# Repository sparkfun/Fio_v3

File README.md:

Fio v3
======

[  
*Fio v3-ATmega32U4 (DEV-11520)*](https://www.sparkfun.com/products/11520)

The Fio v3 is a ATmega32U4 powered system, similar to the ARduino Fio. This board is compatible with a Lipo battery and XBees, and 
runs at 3.3v and 8MHz. 

Repository Contents
-------------------
* **/Firmware** - Arduino example code used in the hookup guide
* **/Hardware** - All Eagle design files (.brd, .sch, .STL)
* **/Production** - Test bed files and production panel files

Documentation
--------------
* **[Hookup Guide](https://learn.sparkfun.com/tutorials/pro-micro--fio-v3-hookup-guide)** - Basic hookup guide for the FioV3.
* **[SparkFun Arduino Board Addon](https://github.com/sparkfun/Arduino_Boards/)** - Arduino board addon for FioV3.
 
License Information
-------------------
This product is _**open source**_! 

Please review the LICENSE.md file for license information. 

If you have any questions or concerns on licensing, please contact techsupport@sparkfun.com.

Distributed as-is; no warranty is given.

- Your friends at SparkFun.

_<COLLABORATION CREDIT>_

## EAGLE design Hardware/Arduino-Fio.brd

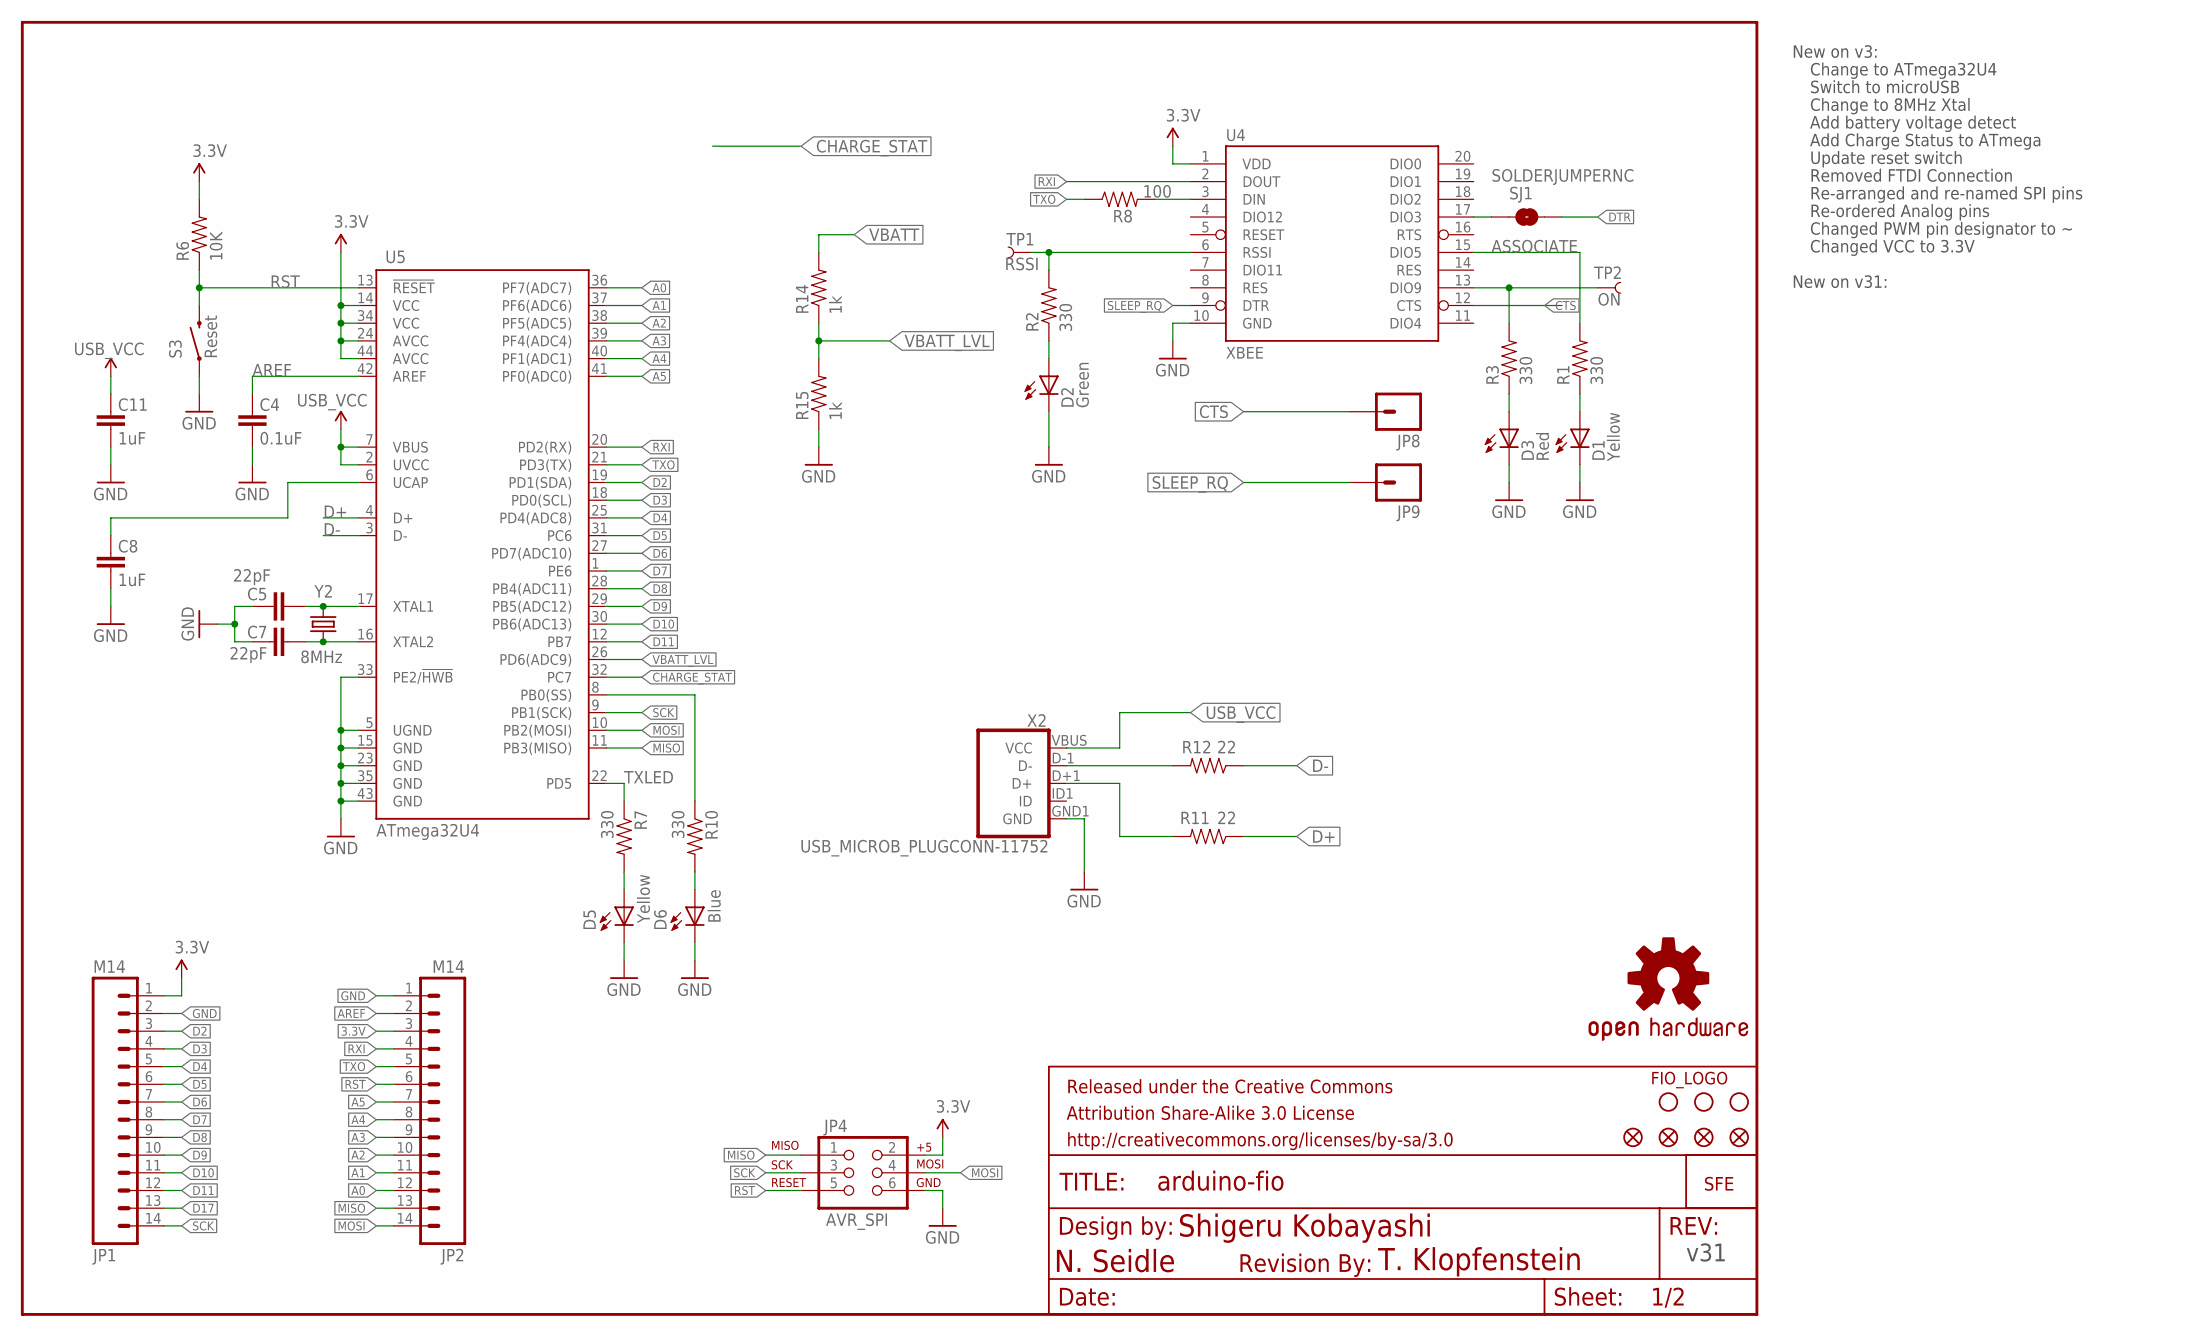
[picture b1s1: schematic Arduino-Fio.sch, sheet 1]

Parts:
C4: 0.1uF; 0603-CAP
C5, C7: 22pF; 0603-CAP
C8, C11: 1uF; 0603-CAP
D1, D5: Yellow; LED-0603
D2: Green; LED-0603
D3: Red; LED-0603
D6: Blue; LED-0603
FRAME1: FRAME-LETTER; CREATIVE_COMMONS
JP1, JP2: M14; 1X14
JP4: AVR_SPI; 2X3
JP5, JP16, JP17: STAND-OFF
JP8, JP9: M01PTH; 1X01
JP10, JP11, JP12, JP13: FIDUCIALUFIDUCIAL; FIDUCIAL-1X2
LOGO1: OSHW-LOGOL; OSHW-LOGO-L
R1, R2, R3, R7, R10: 330; 0603-RES
R6: 10K; 0603-RES
R8: 100; 0603-RES
R11, R12: 22; 0603-RES
R14, R15: 1k; 0603-RES
S3: Reset; TACTILE_SWITCH_SMD
SJ1: SOLDERJUMPERNC; SJ_2S
TP1: RSSI; PAD.03X.05
TP2: ON; PAD.03X.05
U4: XBEE; XBEE-SMD
U5: ATmega32U4; QFN-44-NOPAD_1:1
U$1: LOGO-SFENEW; SFE-NEW-WEBLOGO
U$2: REVISION
U$6: FIO_LOGOV2; FUNNEL_LOGO_BOTTOM_V2
X2: USB_MICROB_PLUGCONN-11752; USB-B-MICRO-SMD_V03
Y2: 8MHz; CRYSTAL-SMD-5X3

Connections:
3.3V: JP1.1, JP2.3, JP4.2, R6.2, U4.1 (VDD), U5.14 (VCC), U5.24 (AVCC), U5.34 (VCC), U5.44 (AVCC); also elsewhere on the board
A0: JP2.12, U5.36 (PF7(ADC7))
A1: JP2.11, U5.37 (PF6(ADC6))
A2: JP2.10, U5.38 (PF5(ADC5))
A3: JP2.9, U5.39 (PF4(ADC4))
A4: JP2.8, U5.40 (PF1(ADC1))
A5: JP2.7, U5.41 (PF0(ADC0))
AREF: C4.2, JP2.2, U5.42 (AREF)
ASSOCIATE: R1.2, U4.15 (DIO5)
CHARGE_STAT: U5.32 (PC7); also elsewhere on the board
CTS: JP8.1, U4.12 (CTS)
D2: JP1.3, U5.19 (PD1(SDA))
D3: JP1.4, U5.18 (PD0(SCL))
D4: JP1.5, U5.25 (PD4(ADC8))
D5: JP1.6, U5.31 (PC6)
D6: JP1.7, U5.27 (PD7(ADC10))
D7: JP1.8, U5.1 (PE6)
D8: JP1.9, U5.28 (PB4(ADC11))
D9: JP1.10, U5.29 (PB5(ADC12))
D10: JP1.11, U5.30 (PB6(ADC13))
D11: JP1.12, U5.12 (PB7)
D17: JP1.13, R10.1, U5.8 (PB0(SS))
D+: R11.1, U5.4 (D+)
D-: R12.1, U5.3 (D-)
DTR: SJ1.2
GND: C4.1, C5.2, C7.2, C8.1, C11.1, D1.C, D2.C, D3.C, D5.C, D6.C, JP1.2, JP2.1, JP4.6, R15.1, S3.1, U4.10 (GND), U5.5 (UGND), U5.15 (GND), U5.23 (GND), U5.33 (PE2/!HWB), U5.35 (GND), U5.43 (GND), X2.GND1 (GND); also elsewhere on the board
MISO: JP2.13, JP4.1, U5.11 (PB3(MISO))
MOSI: JP2.14, JP4.4, U5.10 (PB2(MOSI))
unnamed: R3.2, TP2.P$1, U4.13 (DIO9)
unnamed: D1.A, R1.1
unnamed: D2.A, R2.1
unnamed: R2.2, TP1.P$1, U4.6 (RSSI)
unnamed: R11.2, X2.D+1 (D+)
unnamed: D3.A, R3.1
unnamed: R8.2, U4.3 (DIN)
unnamed: SJ1.1, U4.17 (DIO3)
unnamed: D5.A, R7.2
unnamed: C7.1, U5.16 (XTAL2), Y2.1
unnamed: C5.1, U5.17 (XTAL1), Y2.3 (2)
unnamed: D6.A, R10.2
unnamed: R12.2, X2.D-1 (D-)
RST: JP2.6, JP4.5, R6.1, S3.3 (2), U5.13 (!RESET)
RXI: JP2.4, U4.2 (DOUT), U5.20 (PD2(RX))
SCK: JP1.14, JP4.3, U5.9 (PB1(SCK))
SLEEP_RQ: JP9.1, U4.9 (DTR)
TXLED: R7.1, U5.22 (PD5)
TXO: JP2.5, R8.1, U5.21 (PD3(TX))
UCAP: C8.2, U5.6 (UCAP)
USB_VCC: C11.2, U5.2 (UVCC), U5.7 (VBUS), X2.VBUS (VCC); also elsewhere on the board
VBATT: R14.2; also elsewhere on the board
VBATT_LVL: R14.1, R15.2, U5.26 (PD6(ADC9))

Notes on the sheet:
Shigeru Kobayashi
Change to ATmega32U4
Switch to microUSB
New on v3:
Change to 8MHz Xtal
Add battery voltage detect
Add Charge Status to ATmega
Update reset switch
Removed FTDI Connection
Re-arranged and re-named SPI pins
Re-ordered Analog pins
Changed PWM pin designator to ~
Changed VCC to 3.3V
New on v31:
v31
N. Seidle
T. Klopfenstein

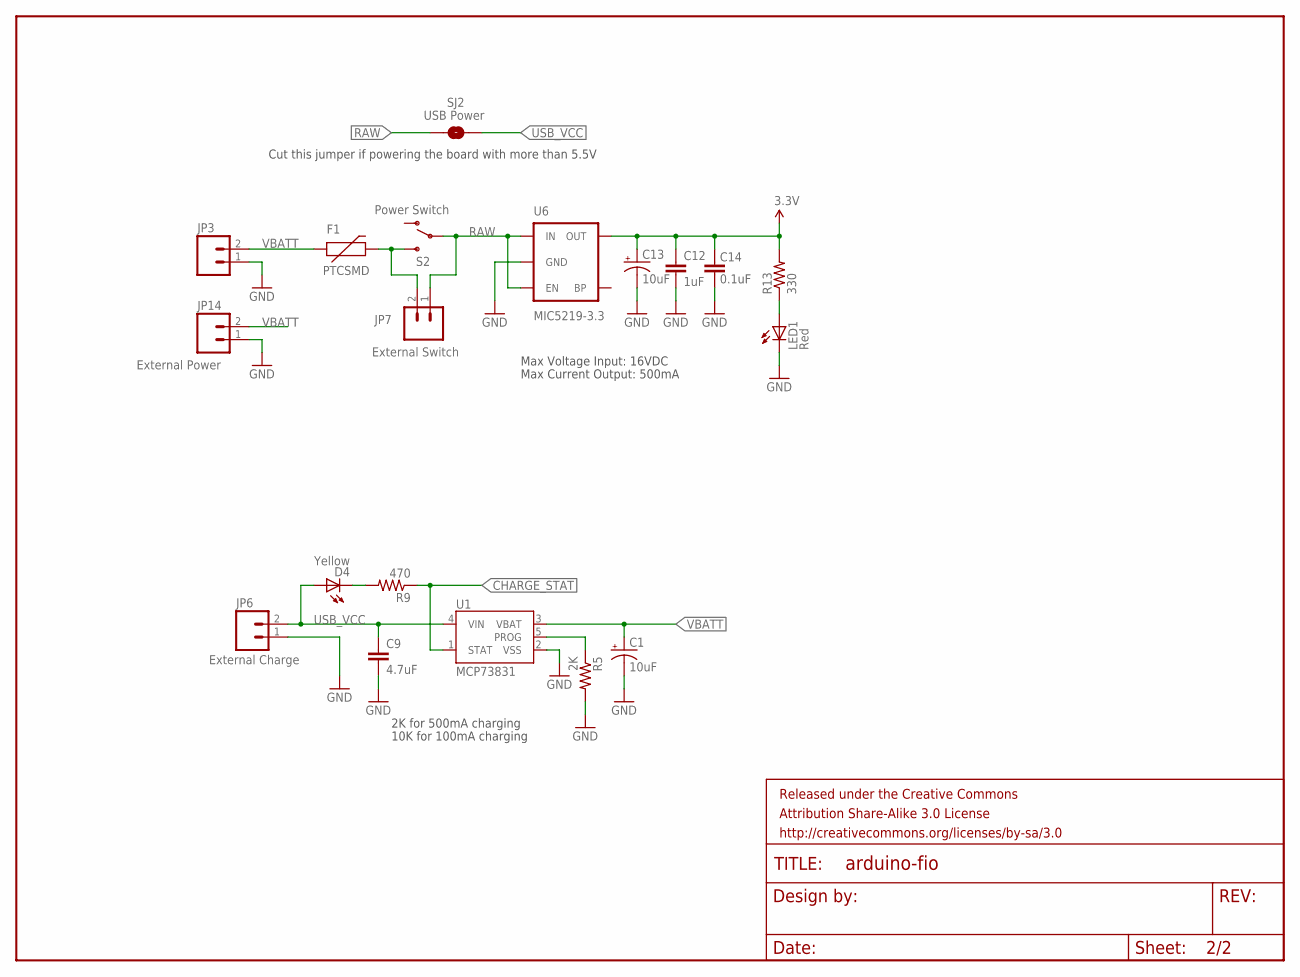
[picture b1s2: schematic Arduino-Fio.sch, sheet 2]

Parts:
C1, C13: 10uF; EIA3216
C9: 4.7uF; 0603-CAP
C12: 1uF; 0603-CAP
C14: 0.1uF; 0603-CAP
D4: Yellow; LED-0603
F1: PTCSMD; PTC-1206
FRAME2: FRAME-LETTER; CREATIVE_COMMONS
JP3: M02-JST-2MM-SMT; JST-2-SMD
JP6: External Charge; 1X02
JP7: External Switch; 1X02
JP14: External Power; 1X02
LED1: Red; LED-0603
R5: 2K; 0603-RES
R9: 470; 0603-RES
R13: 330; 0603-RES
S2: Power Switch; AYZ0202
SJ2: USB Power; SJ_2S-TRACE
U1: MCP73831; SOT23-5
U6: MIC5219-3.3; SOT23-5

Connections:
3.3V: C12.1, C13.A (+), C14.2, R13.2, U6.5 (OUT); also elsewhere on the board
CHARGE_STAT: R9.1, U1.1 (STAT); also elsewhere on the board
GND: C1.C (-), C9.2, C12.2, C13.C (-), C14.1, JP3.1, JP6.1, JP14.1, LED1.C, R5.2, U1.2 (VSS), U6.2 (GND); also elsewhere on the board
unnamed: D4.C, R9.2
unnamed: F1.2, JP7.2, S2.3 (S)
unnamed: R5.1, U1.5 (PROG)
unnamed: LED1.A, R13.1
RAW: JP7.1, S2.2, SJ2.1, U6.1 (IN), U6.3 (EN)
USB_VCC: C9.1, D4.A, JP6.2, SJ2.2, U1.4 (VIN); also elsewhere on the board
VBATT: C1.A (+), F1.1, JP3.2, JP14.2, U1.3 (VBAT); also elsewhere on the board

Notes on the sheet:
Max Voltage Input: 16VDC
Max Current Output: 500mA
Cut this jumper if powering the board with more than 5.5V
2K for 500mA charging
10K for 100mA charging

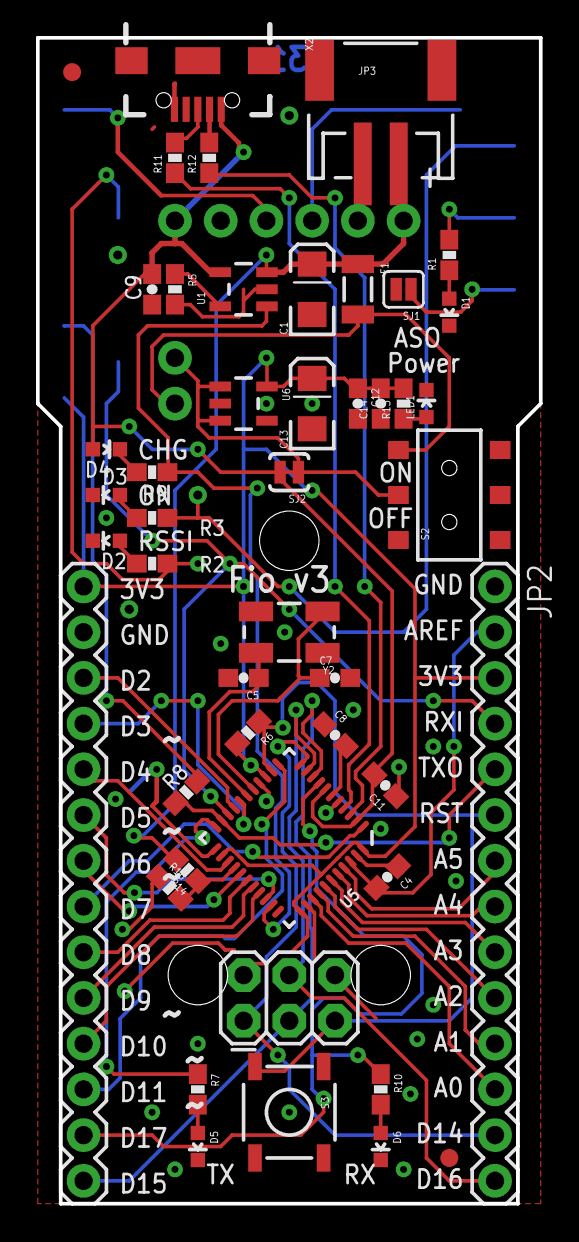
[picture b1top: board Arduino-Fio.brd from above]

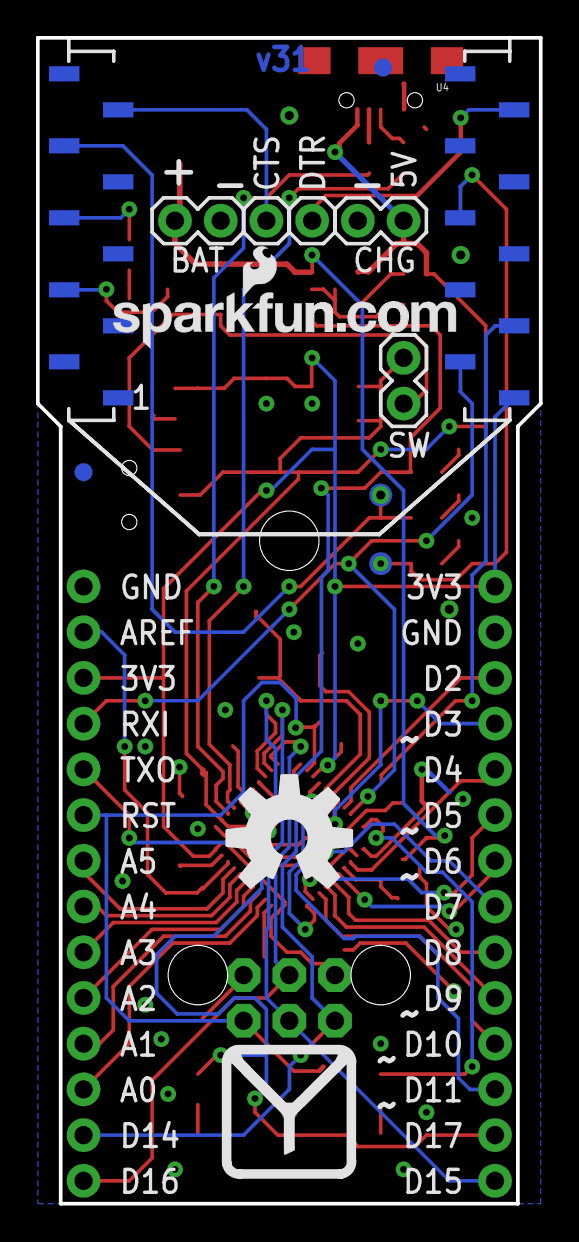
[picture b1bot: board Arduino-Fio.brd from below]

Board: 2 copper layers, 27.9 x 64.8 mm, 66 parts (12 on the bottom side), 55 nets.

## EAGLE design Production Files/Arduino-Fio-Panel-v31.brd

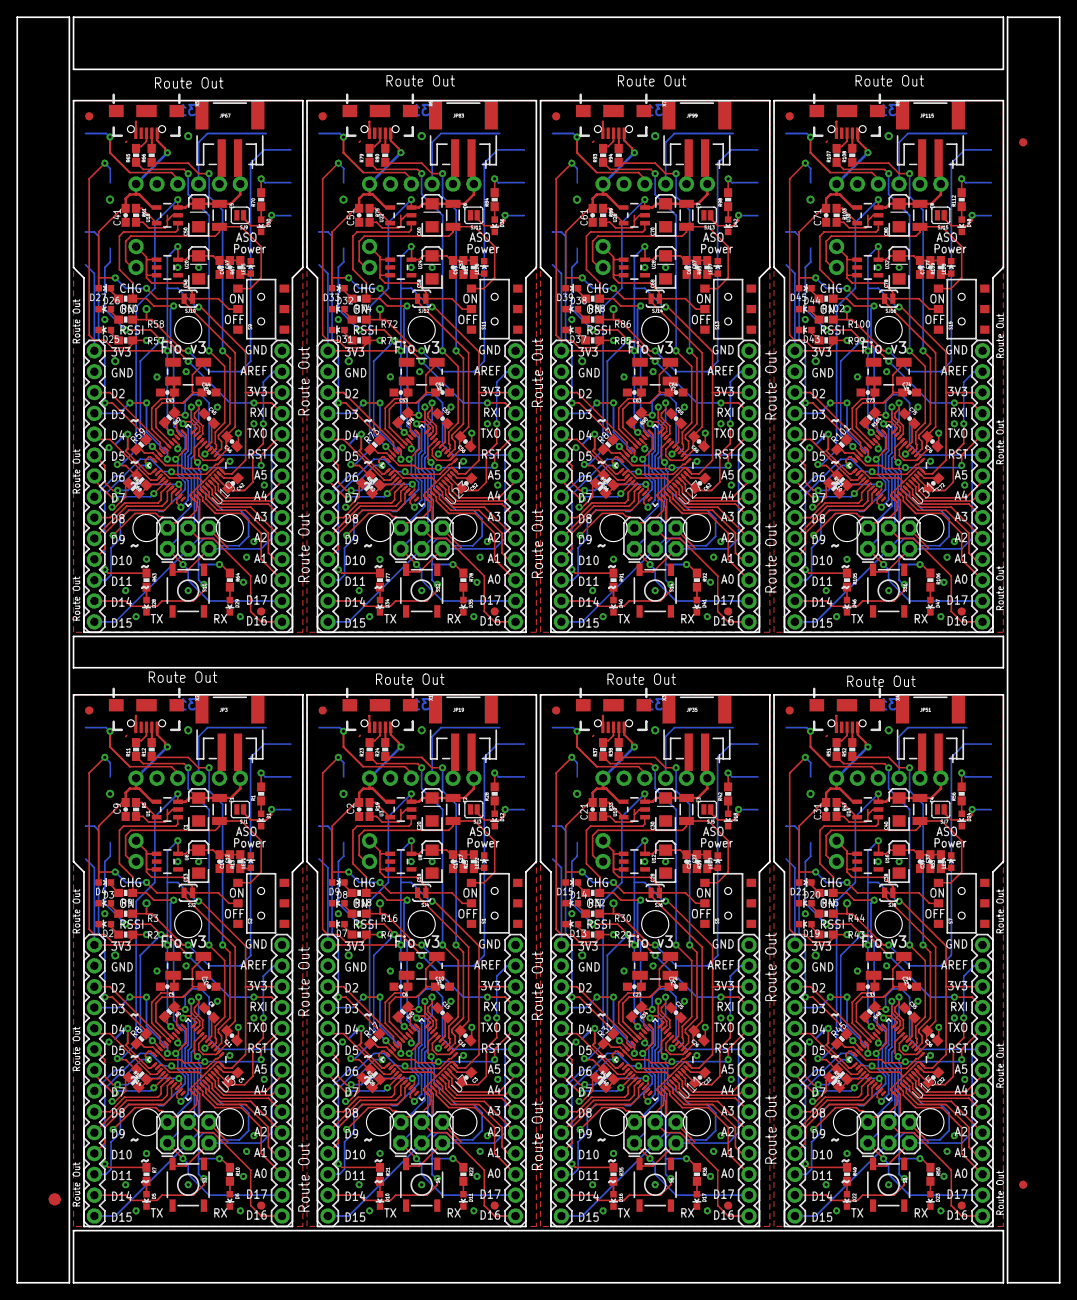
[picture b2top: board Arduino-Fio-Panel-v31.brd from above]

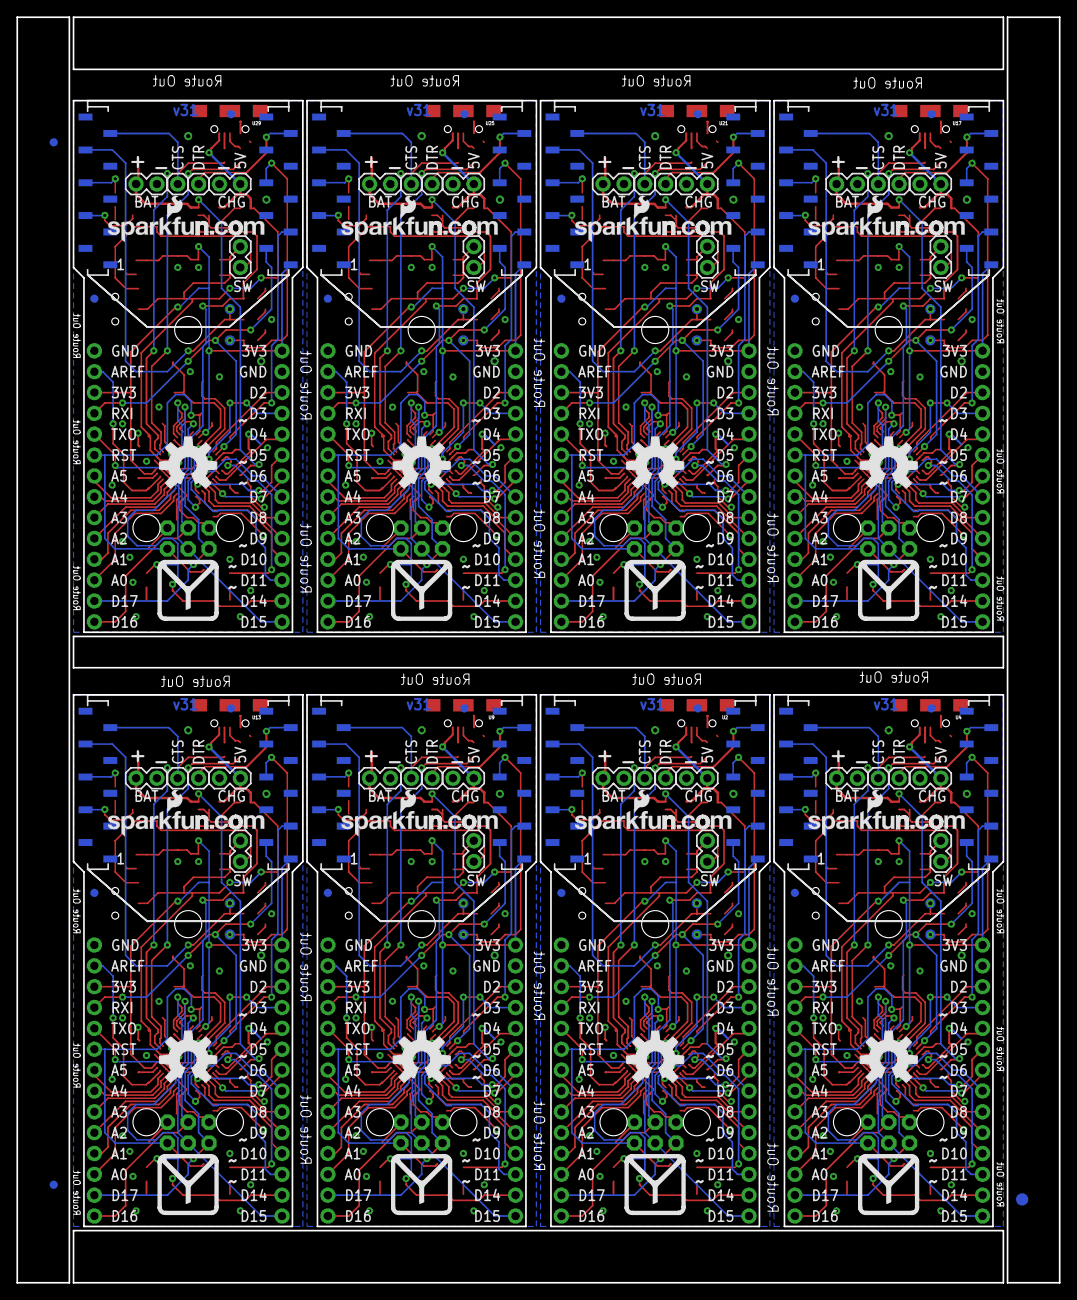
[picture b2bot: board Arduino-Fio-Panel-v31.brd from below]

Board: 2 copper layers, 127.0 x 154.2 mm, 510 parts (99 on the bottom side), 440 nets.

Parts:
C1, C13, C18, C20, C28, C30, C38, C40, C48, C50, C58, C60, C68, C70, C78, C80: 10uF; EIA3216
C2, C9, C21, C31, C41, C51, C61, C71: 4.7uF; 0603-CAP
C3, C4, C14, C19, C22, C29, C32, C39, C42, C49, C52, C59, C62, C69, C72, C79: 0.1uF; 0603-CAP
C5, C6, C7, C10, C23, C24, C33, C34, C43, C44, C53, C54, C63, C64, C73, C74: 22pF; 0603-CAP
C8, C11, C12, C15, C16, C17, C25, C26, C27, C35, C36, C37, C45, C46, C47, C55, C56, C57, C65, C66, C67, C75, C76, C77: 1uF; 0603-CAP
D1, D4, D5, D9, D10, D12, D15, D16, D18, D21, D22, D24, D27, D28, D30, D33, D34, D36, D39, D40, D42, D45, D46, D48: Yellow; LED-0603
D2, D7, D13, D19, D25, D31, D37, D43: Green; LED-0603
D3, D8, D14, D20, D26, D32, D38, D44: Red; LED-0603
D6, D11, D17, D23, D29, D35, D41, D47: Blue; LED-0603
E$1, E$2: FIDUCIAL-1.5X3
E$3, E$4, E$5, E$6: FIDUCIAL-1X2
F1, F2, F3, F4, F5, F6, F7, F8: PTCSMD; PTC-1206
JP1, JP2, JP18, JP29, JP34, JP45, JP50, JP61, JP66, JP77, JP82, JP93, JP98, JP109, JP114, JP125: M14; 1X14
JP3, JP19, JP35, JP51, JP67, JP83, JP99, JP115: JST-2-SMD
JP4, JP15, JP33, JP49, JP65, JP81, JP97, JP113: AVR_SPI; 2X3
JP5, JP16, JP17, JP30, JP31, JP32, JP46, JP47, JP48, JP62, JP63, JP64, JP78, JP79, JP80, JP94, JP95, JP96, JP110, JP111, JP112, JP126, JP127, JP128: STAND-OFF
JP6, JP21, JP37, JP53, JP69, JP85, JP101, JP117: External Charge; 1X02
JP7, JP22, JP38, JP54, JP70, JP86, JP102, JP118: External Switch; 1X02
JP8, JP9, JP23, JP24, JP39, JP40, JP55, JP56, JP71, JP72, JP87, JP88, JP103, JP104, JP119, JP120: 1X01
JP10, JP11, JP12, JP13, JP25, JP26, JP27, JP28, JP41, JP42, JP43, JP44, JP57, JP58, JP59, JP60, JP73, JP74, JP75, JP76, JP89, JP90, JP91, JP92, JP105, JP106, JP107, JP108, JP121, JP122, JP123, JP124: FIDUCIALUFIDUCIAL; FIDUCIAL-1X2
JP14, JP20, JP36, JP52, JP68, JP84, JP100, JP116: External Power; 1X02
LED1, LED2, LED3, LED4, LED5, LED6, LED7, LED8: Red; LED-0603
LOGO1, LOGO2, LOGO3, LOGO4, LOGO5, LOGO6, LOGO7, LOGO8: OSHW-LOGOL; OSHW-LOGO-L
R1, R2, R3, R4, R7, R10, R13, R16, R21, R22, R25, R28, R29, R30, R35, R36, R39, R42, R43, R44, R49, R50, R53, R56, R57, R58, R63, R64, R67, R70, R71, R72, R77, R78, R81, R84, R85, R86, R91, R92, R95, R98, R99, R100, R105, R106, R109, R112: 330; 0603-RES
R5, R19, R33, R47, R61, R75, R89, R103: 2K; 0603-RES
R6, R20, R34, R48, R62, R76, R90, R104: 10K; 0603-RES
R8, R17, R31, R45, R59, R73, R87, R101: 100; 0603-RES
R9, R18, R32, R46, R60, R74, R88, R102: 470; 0603-RES
R11, R12, R23, R24, R37, R38, R51, R52, R65, R66, R79, R80, R93, R94, R107, R108: 22; 0603-RES
R14, R15, R26, R27, R40, R41, R54, R55, R68, R69, R82, R83, R96, R97, R110, R111: 1k; 0603-RES
S1, S2, S5, S7, S9, S11, S13, S15: Power Switch; AYZ0202
S3, S4, S6, S8, S10, S12, S14, S16: Reset; TACTILE_SWITCH_SMD
SJ1, SJ3, SJ5, SJ7, SJ9, SJ11, SJ13, SJ15: SOLDERJUMPERNC; SJ_2S
SJ2, SJ4, SJ6, SJ8, SJ10, SJ12, SJ14, SJ16: USB Power; SJ_2S-TRACE
TP1, TP3, TP5, TP7, TP9, TP11, TP13, TP15: RSSI; PAD.03X.05
TP2, TP4, TP6, TP8, TP10, TP12, TP14, TP16: ON; PAD.03X.05
U1, U3, U10, U14, U18, U22, U26, U30: MCP73831; SOT23-5
U2, U4, U9, U13, U17, U21, U25, U29: XBEE; XBEE-SMD
U5, U7, U11, U15, U19, U23, U27, U31: ATMEGA32U4; QFN-44-NOPAD_1:1
U6, U8, U12, U16, U20, U24, U28, U32: MIC5219-3.3; SOT23-5
U$1, U$2, U$4, U$7, U$9, U$11, U$13, U$15: LOGO-SFENEW; SFE-NEW-WEBLOGO
U$3, U$5, U$6, U$8, U$10, U$12, U$14, U$16: FIO_LOGOV2; FUNNEL_LOGO_BOTTOM_V2
X1, X2, X3, X4, X5, X6, X7, X8: USB_MICROB_PLUGCONN-11752; USB-B-MICRO-SMD_V03
Y1, Y2, Y3, Y4, Y5, Y6, Y7, Y8: 8MHz; CRYSTAL-SMD-5X3

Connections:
3.3V: C12.1, C13.A, C14.2, JP1.1, JP2.3, JP4.2, R6.2, R13.2, U4.1, U5.14, U5.24, U5.34, U5.44, U6.5
3.3V1: C17.1, C18.A, C19.2, JP15.2, JP18.1, JP29.3, R20.2, R25.2, U2.1, U7.14, U7.24, U7.34, U7.44, U8.5
3.3V2: C27.1, C28.A, C29.2, JP33.2, JP34.1, JP45.3, R34.2, R39.2, U9.1, U11.14, U11.24, U11.34, U11.44, U12.5
3.3V3: C37.1, C38.A, C39.2, JP49.2, JP50.1, JP61.3, R48.2, R53.2, U13.1, U15.14, U15.24, U15.34, U15.44, U16.5
3.3V4: C47.1, C48.A, C49.2, JP65.2, JP66.1, JP77.3, R62.2, R67.2, U17.1, U19.14, U19.24, U19.34, U19.44, U20.5
3.3V5: C57.1, C58.A, C59.2, JP81.2, JP82.1, JP93.3, R76.2, R81.2, U21.1, U23.14, U23.24, U23.34, U23.44, U24.5
3.3V6: C67.1, C68.A, C69.2, JP97.2, JP98.1, JP109.3, R90.2, R95.2, U25.1, U27.14, U27.24, U27.34, U27.44, U28.5
3.3V7: C77.1, C78.A, C79.2, JP113.2, JP114.1, JP125.3, R104.2, R109.2, U29.1, U31.14, U31.24, U31.34, U31.44, U32.5
A0: JP2.12, U5.36
A1: JP2.11, U5.37
A2: JP2.10, U5.38
A3: JP2.9, U5.39
A4: JP2.8, U5.40
A5: JP2.7, U5.41
A6: JP29.12, U7.36
A7: JP29.11, U7.37
A8: JP29.10, U7.38
A9: JP29.9, U7.39
A10: JP29.8, U7.40
A11: JP29.7, U7.41
A12: JP45.12, U11.36
A13: JP45.11, U11.37
A14: JP45.10, U11.38
A15: JP45.9, U11.39
A16: JP45.8, U11.40
A17: JP45.7, U11.41
A18: JP61.12, U15.36
A19: JP61.11, U15.37
A20: JP61.10, U15.38
A21: JP61.9, U15.39
A22: JP61.8, U15.40
A23: JP61.7, U15.41
A24: JP77.12, U19.36
A25: JP77.11, U19.37
A26: JP77.10, U19.38
A27: JP77.9, U19.39
A28: JP77.8, U19.40
A29: JP77.7, U19.41
A30: JP93.12, U23.36
A31: JP93.11, U23.37
A32: JP93.10, U23.38
A33: JP93.9, U23.39
A34: JP93.8, U23.40
A35: JP93.7, U23.41
A36: JP109.12, U27.36
A37: JP109.11, U27.37
A38: JP109.10, U27.38
A39: JP109.9, U27.39
A40: JP109.8, U27.40
A41: JP109.7, U27.41
A42: JP125.12, U31.36
A43: JP125.11, U31.37
A44: JP125.10, U31.38
A45: JP125.9, U31.39
A46: JP125.8, U31.40
A47: JP125.7, U31.41
AREF: C4.2, JP2.2, U5.42
AREF1: C3.2, JP29.2, U7.42
AREF2: C22.2, JP45.2, U11.42
AREF3: C32.2, JP61.2, U15.42
AREF4: C42.2, JP77.2, U19.42
AREF5: C52.2, JP93.2, U23.42
AREF6: C62.2, JP109.2, U27.42
AREF7: C72.2, JP125.2, U31.42
ASSOCIATE: R1.2, U4.15
ASSOCIATE1: R28.2, U2.15
ASSOCIATE2: R42.2, U9.15
ASSOCIATE3: R56.2, U13.15
ASSOCIATE4: R70.2, U17.15
ASSOCIATE5: R84.2, U21.15
ASSOCIATE6: R98.2, U25.15
ASSOCIATE7: R112.2, U29.15
CHARGE_STAT: R9.1, U1.1, U5.32
CHARGE_STAT1: R18.1, U3.1, U7.32
CHARGE_STAT2: R32.1, U10.1, U11.32
CHARGE_STAT3: R46.1, U14.1, U15.32
CHARGE_STAT4: R60.1, U18.1, U19.32
CHARGE_STAT5: R74.1, U22.1, U23.32
CHARGE_STAT6: R88.1, U26.1, U27.32
CHARGE_STAT7: R102.1, U30.1, U31.32
CTS: JP8.1, U4.12
CTS1: JP23.1, U2.12
CTS2: JP39.1, U9.12
CTS3: JP55.1, U13.12
CTS4: JP71.1, U17.12
CTS5: JP87.1, U21.12
CTS6: JP103.1, U25.12
CTS7: JP119.1, U29.12
D1: JP18.3, U7.19
D2: JP1.3, U5.19
D3: JP1.4, U5.18
D4: JP1.5, U5.25
D5: JP1.6, U5.31
D6: JP1.7, U5.27
D7: JP1.8, U5.1
D8: JP1.9, U5.28
D9: JP1.10, U5.29
D10: JP1.11, U5.30
D11: JP1.12, U5.12
D12: JP18.4, U7.18
D13: JP18.5, U7.25
D14: JP1.13, R10.1, U5.8
D15: JP18.6, U7.31
D16: JP18.7, U7.27
D17: JP18.9, U7.28
D18: JP18.11, U7.30
D19: JP18.8, U7.1
D20: JP18.10, U7.29
D21: JP18.12, U7.12
D22: JP18.13, R22.1, U7.8
D23: JP34.3, U11.19
D24: JP34.4, U11.18
D25: JP34.5, U11.25
D26: JP34.6, U11.31
D27: JP34.7, U11.27
D28: JP34.9, U11.28
D29: JP34.11, U11.30
D30: JP34.8, U11.1
D31: JP34.10, U11.29
D32: JP34.12, U11.12
D33: JP34.13, R36.1, U11.8
D34: JP50.3, U15.19
D35: JP50.4, U15.18
D36: JP50.5, U15.25
D37: JP50.6, U15.31
D38: JP50.7, U15.27
D39: JP50.9, U15.28
D40: JP50.11, U15.30
D41: JP50.8, U15.1
D42: JP50.10, U15.29
D43: JP50.12, U15.12
D44: JP50.13, R50.1, U15.8
D45: JP66.3, U19.19
D46: JP66.4, U19.18
D47: JP66.5, U19.25
D48: JP66.6, U19.31
D49: JP66.7, U19.27
D50: JP66.9, U19.28
D51: JP66.11, U19.30
D52: JP66.8, U19.1
D53: JP66.10, U19.29
D54: JP66.12, U19.12
D55: JP66.13, R64.1, U19.8
D56: JP82.3, U23.19
D57: JP82.4, U23.18
D58: JP82.5, U23.25
D59: JP82.6, U23.31
D60: JP82.7, U23.27
D61: JP82.9, U23.28
D62: JP82.11, U23.30
D63: JP82.8, U23.1
D64: JP82.10, U23.29
D65: JP82.12, U23.12
D66: JP82.13, R78.1, U23.8
D67: JP98.3, U27.19
D68: JP98.4, U27.18
D69: JP98.5, U27.25
D70: JP98.6, U27.31
D71: JP98.7, U27.27
D72: JP98.9, U27.28
D73: JP98.11, U27.30
D74: JP98.8, U27.1
D75: JP98.10, U27.29
D76: JP98.12, U27.12
D77: JP98.13, R92.1, U27.8
D78: JP114.3, U31.19
D79: JP114.4, U31.18
D80: JP114.5, U31.25
D81: JP114.6, U31.31
D82: JP114.7, U31.27
D83: JP114.9, U31.28
D84: JP114.11, U31.30
D85: JP114.8, U31.1
D86: JP114.10, U31.29
D87: JP114.12, U31.12
D88: JP114.13, R106.1, U31.8
D+: R11.1, U5.4
D+1: R23.1, U7.4
D+2: R37.1, U11.4
D+3: R51.1, U15.4
D+4: R65.1, U19.4
D+5: R79.1, U23.4
D+6: R93.1, U27.4
D+7: R107.1, U31.4
D-: R12.1, U5.3
D-1: R24.1, U7.3
D-2: R38.1, U11.3
D-3: R52.1, U15.3
D-4: R66.1, U19.3
D-5: R80.1, U23.3
D-6: R94.1, U27.3
D-7: R108.1, U31.3
GND: C1.C, C4.1, C5.2, C7.2, C8.1, C9.2, C11.1, C12.2, C13.C, C14.1, D1.C, D2.C, D3.C, D5.C, D6.C, JP1.2, JP2.1, JP3.1, JP4.6, JP6.1, JP14.1, LED1.C, R5.2, R15.1, S3.1, U1.2, U4.10, U5.5, U5.15, U5.23, U5.33, U5.35, U5.43, U6.2, X2.GND1
GND1: C2.2, C3.1, C6.2, C10.2, C15.1, C16.1, C17.2, C18.C, C19.1, C20.C, D7.C, D8.C, D10.C, D11.C, D12.C, JP15.6, JP18.2, JP19.1, JP20.1, JP21.1, JP29.1, LED2.C, R19.2, R27.1, S4.1, U2.10, U3.2, U7.5, U7.15, U7.23, U7.33, U7.35, U7.43, U8.2, X1.GND1
GND2: C21.2, C22.1, C23.2, C24.2, C25.1, C26.1, C27.2, C28.C, C29.1, C30.C, D13.C, D14.C, D16.C, D17.C, D18.C, JP33.6, JP34.2, JP35.1, JP36.1, JP37.1, JP45.1, LED3.C, R33.2, R41.1, S6.1, U9.10, U10.2, U11.5, U11.15, U11.23, U11.33, U11.35, U11.43, U12.2, X3.GND1
GND3: C31.2, C32.1, C33.2, C34.2, C35.1, C36.1, C37.2, C38.C, C39.1, C40.C, D19.C, D20.C, D22.C, D23.C, D24.C, JP49.6, JP50.2, JP51.1, JP52.1, JP53.1, JP61.1, LED4.C, R47.2, R55.1, S8.1, U13.10, U14.2, U15.5, U15.15, U15.23, U15.33, U15.35, U15.43, U16.2, X4.GND1
GND4: C41.2, C42.1, C43.2, C44.2, C45.1, C46.1, C47.2, C48.C, C49.1, C50.C, D25.C, D26.C, D28.C, D29.C, D30.C, JP65.6, JP66.2, JP67.1, JP68.1, JP69.1, JP77.1, LED5.C, R61.2, R69.1, S10.1, U17.10, U18.2, U19.5, U19.15, U19.23, U19.33, U19.35, U19.43, U20.2, X5.GND1
GND5: C51.2, C52.1, C53.2, C54.2, C55.1, C56.1, C57.2, C58.C, C59.1, C60.C, D31.C, D32.C, D34.C, D35.C, D36.C, JP81.6, JP82.2, JP83.1, JP84.1, JP85.1, JP93.1, LED6.C, R75.2, R83.1, S12.1, U21.10, U22.2, U23.5, U23.15, U23.23, U23.33, U23.35, U23.43, U24.2, X6.GND1
GND6: C61.2, C62.1, C63.2, C64.2, C65.1, C66.1, C67.2, C68.C, C69.1, C70.C, D37.C, D38.C, D40.C, D41.C, D42.C, JP97.6, JP98.2, JP99.1, JP100.1, JP101.1, JP109.1, LED7.C, R89.2, R97.1, S14.1, U25.10, U26.2, U27.5, U27.15, U27.23, U27.33, U27.35, U27.43, U28.2, X7.GND1
GND7: C71.2, C72.1, C73.2, C74.2, C75.1, C76.1, C77.2, C78.C, C79.1, C80.C, D43.C, D44.C, D46.C, D47.C, D48.C, JP113.6, JP114.2, JP115.1, JP116.1, JP117.1, JP125.1, LED8.C, R103.2, R111.1, S16.1, U29.10, U30.2, U31.5, U31.15, U31.23, U31.33, U31.35, U31.43, U32.2, X8.GND1
MISO: JP2.13, JP4.1, U5.11
MISO1: JP15.1, JP29.13, U7.11
MISO2: JP33.1, JP45.13, U11.11
MISO3: JP49.1, JP61.13, U15.11
MISO4: JP65.1, JP77.13, U19.11
MISO5: JP81.1, JP93.13, U23.11
MISO6: JP97.1, JP109.13, U27.11
MISO7: JP113.1, JP125.13, U31.11
MOSI: JP2.14, JP4.4, U5.10
MOSI1: JP15.4, JP29.14, U7.10
MOSI2: JP33.4, JP45.14, U11.10
MOSI3: JP49.4, JP61.14, U15.10
MOSI4: JP65.4, JP77.14, U19.10
MOSI5: JP81.4, JP93.14, U23.10
MOSI6: JP97.4, JP109.14, U27.10
MOSI7: JP113.4, JP125.14, U31.10
unnamed: R3.2, TP2.P$1, U4.13
unnamed: D1.A, R1.1
unnamed: D2.A, R2.1
unnamed: R2.2, TP1.P$1, U4.6
unnamed: R11.2, X2.D+1
unnamed: D3.A, R3.1
unnamed: R8.2, U4.3
unnamed: D4.C, R9.2
unnamed: F1.2, JP7.2, S2.3
unnamed: D7.A, R4.1
unnamed: R5.1, U1.5
unnamed: R4.2, TP3.P$1, U2.6
unnamed: SJ1.1, U4.17
unnamed: D8.A, R16.1
unnamed: D5.A, R7.2
unnamed: C7.1, U5.16, Y2.1
unnamed: C5.1, U5.17, Y2.3
unnamed: R16.2, TP4.P$1, U2.13
unnamed: D6.A, R10.2
unnamed: R12.2, X2.D-1
unnamed: R17.2, U2.3
unnamed: F2.2, JP22.2, S1.3
unnamed: SJ3.1, U2.17
unnamed: R19.1, U3.5
unnamed: D9.C, R18.2
unnamed: D10.A, R21.2
unnamed: C10.1, U7.16, Y1.1
unnamed: C6.1, U7.17, Y1.3
unnamed: D11.A, R22.2
unnamed: R24.2, X1.D-1
unnamed: LED2.A, R25.1
unnamed: D12.A, R28.1
unnamed: R23.2, X1.D+1
unnamed: D13.A, R29.1
unnamed: R29.2, TP5.P$1, U9.6
unnamed: D14.A, R30.1
unnamed: R30.2, TP6.P$1, U9.13
unnamed: LED1.A, R13.1
unnamed: R31.2, U9.3
unnamed: F3.2, JP38.2, S5.3
unnamed: SJ5.1, U9.17
unnamed: R33.1, U10.5
unnamed: D15.C, R32.2
unnamed: D16.A, R35.2
unnamed: C24.1, U11.16, Y3.1
unnamed: C23.1, U11.17, Y3.3
unnamed: D17.A, R36.2
unnamed: R38.2, X3.D-1
unnamed: LED3.A, R39.1
unnamed: D18.A, R42.1
unnamed: R37.2, X3.D+1
unnamed: D19.A, R43.1
unnamed: R43.2, TP7.P$1, U13.6
unnamed: D20.A, R44.1
unnamed: R44.2, TP8.P$1, U13.13
unnamed: R45.2, U13.3
unnamed: F4.2, JP54.2, S7.3
unnamed: SJ7.1, U13.17
unnamed: R47.1, U14.5
unnamed: D21.C, R46.2
unnamed: D22.A, R49.2
unnamed: C34.1, U15.16, Y4.1
unnamed: C33.1, U15.17, Y4.3
unnamed: D23.A, R50.2
unnamed: R52.2, X4.D-1
unnamed: LED4.A, R53.1
unnamed: D24.A, R56.1
unnamed: R51.2, X4.D+1
unnamed: D25.A, R57.1
unnamed: R57.2, TP9.P$1, U17.6
unnamed: D26.A, R58.1
unnamed: R58.2, TP10.P$1, U17.13
unnamed: R59.2, U17.3
unnamed: F5.2, JP70.2, S9.3
unnamed: SJ9.1, U17.17
unnamed: R61.1, U18.5
unnamed: D27.C, R60.2
unnamed: D28.A, R63.2
unnamed: C44.1, U19.16, Y5.1
unnamed: C43.1, U19.17, Y5.3
unnamed: D29.A, R64.2
unnamed: R66.2, X5.D-1
unnamed: LED5.A, R67.1
unnamed: D30.A, R70.1
unnamed: R65.2, X5.D+1
unnamed: D31.A, R71.1
unnamed: R71.2, TP11.P$1, U21.6
unnamed: D32.A, R72.1
unnamed: R72.2, TP12.P$1, U21.13
unnamed: R73.2, U21.3
unnamed: F6.2, JP86.2, S11.3
unnamed: SJ11.1, U21.17
unnamed: R75.1, U22.5
unnamed: D33.C, R74.2
unnamed: D34.A, R77.2
unnamed: C54.1, U23.16, Y6.1
unnamed: C53.1, U23.17, Y6.3
unnamed: D35.A, R78.2
unnamed: R80.2, X6.D-1
unnamed: LED6.A, R81.1
unnamed: D36.A, R84.1
unnamed: R79.2, X6.D+1
unnamed: D37.A, R85.1
unnamed: R85.2, TP13.P$1, U25.6
unnamed: D38.A, R86.1
unnamed: R86.2, TP14.P$1, U25.13
unnamed: R87.2, U25.3
unnamed: F7.2, JP102.2, S13.3
unnamed: SJ13.1, U25.17
unnamed: R89.1, U26.5
unnamed: D39.C, R88.2
unnamed: D40.A, R91.2
unnamed: C64.1, U27.16, Y7.1
unnamed: C63.1, U27.17, Y7.3
unnamed: D41.A, R92.2
unnamed: R94.2, X7.D-1
unnamed: LED7.A, R95.1
unnamed: D42.A, R98.1
unnamed: R93.2, X7.D+1
unnamed: D43.A, R99.1
unnamed: R99.2, TP15.P$1, U29.6
unnamed: D44.A, R100.1
unnamed: R100.2, TP16.P$1, U29.13
unnamed: R101.2, U29.3
unnamed: F8.2, JP118.2, S15.3
unnamed: SJ15.1, U29.17
unnamed: R103.1, U30.5
unnamed: D45.C, R102.2
unnamed: D46.A, R105.2
unnamed: C74.1, U31.16, Y8.1
unnamed: C73.1, U31.17, Y8.3
unnamed: D47.A, R106.2
unnamed: R108.2, X8.D-1
unnamed: LED8.A, R109.1
unnamed: D48.A, R112.1
unnamed: R107.2, X8.D+1
RAW: JP7.1, S2.2, SJ2.1, U6.1, U6.3
RAW1: JP22.1, S1.2, SJ4.1, U8.1, U8.3
RAW2: JP38.1, S5.2, SJ6.1, U12.1, U12.3
RAW3: JP54.1, S7.2, SJ8.1, U16.1, U16.3
RAW4: JP70.1, S9.2, SJ10.1, U20.1, U20.3
RAW5: JP86.1, S11.2, SJ12.1, U24.1, U24.3
RAW6: JP102.1, S13.2, SJ14.1, U28.1, U28.3
RAW7: JP118.1, S15.2, SJ16.1, U32.1, U32.3
RST: JP2.6, JP4.5, R6.1, S3.3, U5.13
RST1: JP15.5, JP29.6, R20.1, S4.3, U7.13
RST2: JP33.5, JP45.6, R34.1, S6.3, U11.13
RST3: JP49.5, JP61.6, R48.1, S8.3, U15.13
RST4: JP65.5, JP77.6, R62.1, S10.3, U19.13
RST5: JP81.5, JP93.6, R76.1, S12.3, U23.13
RST6: JP97.5, JP109.6, R90.1, S14.3, U27.13
RST7: JP113.5, JP125.6, R104.1, S16.3, U31.13
RXI: JP2.4, U4.2, U5.20
RXI1: JP29.4, U2.2, U7.20
RXI2: JP45.4, U9.2, U11.20
RXI3: JP61.4, U13.2, U15.20
RXI4: JP77.4, U17.2, U19.20
RXI5: JP93.4, U21.2, U23.20
RXI6: JP109.4, U25.2, U27.20
RXI7: JP125.4, U29.2, U31.20
SCK: JP1.14, JP4.3, U5.9
SCK1: JP15.3, JP18.14, U7.9
SCK2: JP33.3, JP34.14, U11.9
SCK3: JP49.3, JP50.14, U15.9
SCK4: JP65.3, JP66.14, U19.9
SCK5: JP81.3, JP82.14, U23.9
SCK6: JP97.3, JP98.14, U27.9
SCK7: JP113.3, JP114.14, U31.9
SLEEP_RQ: JP9.1, U4.9
SLEEP_RQ1: JP24.1, U2.9
SLEEP_RQ2: JP40.1, U9.9
SLEEP_RQ3: JP56.1, U13.9
SLEEP_RQ4: JP72.1, U17.9
SLEEP_RQ5: JP88.1, U21.9
SLEEP_RQ6: JP104.1, U25.9
SLEEP_RQ7: JP120.1, U29.9
TXLED: R7.1, U5.22
TXLED1: R21.1, U7.22
TXLED2: R35.1, U11.22
TXLED3: R49.1, U15.22
TXLED4: R63.1, U19.22
TXLED5: R77.1, U23.22
TXLED6: R91.1, U27.22
TXLED7: R105.1, U31.22
TXO: JP2.5, R8.1, U5.21
TXO1: JP29.5, R17.1, U7.21
TXO2: JP45.5, R31.1, U11.21
TXO3: JP61.5, R45.1, U15.21
TXO4: JP77.5, R59.1, U19.21
TXO5: JP93.5, R73.1, U23.21
TXO6: JP109.5, R87.1, U27.21
TXO7: JP125.5, R101.1, U31.21
UCAP: C8.2, U5.6
UCAP1: C15.2, U7.6
UCAP2: C25.2, U11.6
UCAP3: C35.2, U15.6
UCAP4: C45.2, U19.6
UCAP5: C55.2, U23.6
UCAP6: C65.2, U27.6
UCAP7: C75.2, U31.6
USB_VCC: C9.1, C11.2, D4.A, JP6.2, SJ2.2, U1.4, U5.2, U5.7, X2.VBUS
USB_VCC1: C2.1, C16.2, D9.A, JP21.2, SJ4.2, U3.4, U7.2, U7.7, X1.VBUS
USB_VCC2: C21.1, C26.2, D15.A, JP37.2, SJ6.2, U10.4, U11.2, U11.7, X3.VBUS
USB_VCC3: C31.1, C36.2, D21.A, JP53.2, SJ8.2, U14.4, U15.2, U15.7, X4.VBUS
USB_VCC4: C41.1, C46.2, D27.A, JP69.2, SJ10.2, U18.4, U19.2, U19.7, X5.VBUS
USB_VCC5: C51.1, C56.2, D33.A, JP85.2, SJ12.2, U22.4, U23.2, U23.7, X6.VBUS
USB_VCC6: C61.1, C66.2, D39.A, JP101.2, SJ14.2, U26.4, U27.2, U27.7, X7.VBUS
USB_VCC7: C71.1, C76.2, D45.A, JP117.2, SJ16.2, U30.4, U31.2, U31.7, X8.VBUS
VBATT: C1.A, F1.1, JP3.2, JP14.2, R14.2, U1.3
VBATT1: C20.A, F2.1, JP19.2, JP20.2, R26.2, U3.3
VBATT2: C30.A, F3.1, JP35.2, JP36.2, R40.2, U10.3
VBATT3: C40.A, F4.1, JP51.2, JP52.2, R54.2, U14.3
VBATT4: C50.A, F5.1, JP67.2, JP68.2, R68.2, U18.3
VBATT5: C60.A, F6.1, JP83.2, JP84.2, R82.2, U22.3
VBATT6: C70.A, F7.1, JP99.2, JP100.2, R96.2, U26.3
VBATT7: C80.A, F8.1, JP115.2, JP116.2, R110.2, U30.3
VBATT_LVL: R14.1, R15.2, U5.26
VBATT_LVL1: R26.1, R27.2, U7.26
VBATT_LVL2: R40.1, R41.2, U11.26
VBATT_LVL3: R54.1, R55.2, U15.26
VBATT_LVL4: R68.1, R69.2, U19.26
VBATT_LVL5: R82.1, R83.2, U23.26
VBATT_LVL6: R96.1, R97.2, U27.26
VBATT_LVL7: R110.1, R111.2, U31.26

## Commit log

2013-07-03 Hardware v31 upload
2013-07-03 Update README.md
    Fixed formatting.
2013-11-07 Midway hardware update
2014-01-02 Fixing USB trace issue
2014-01-31 Fixing schematic frame
2014-02-05 Moved bottom fiducials to clear the Xbee headers
2014-02-05 Created Panel v31
2018-01-29 Update README.md
    * Link Tutorial
    * Link Board Addon repo
    *Update License
2018-01-29 Create Blinkies.ino
    Example code used in the hookup guide.
2018-01-29 Rename Blinkies/Blinkies.ino to Firmware/Blinkies/Blinkies.ino
2019-02-11 Update Labeling
    Updated individual board's silkscreen to correct pins to match the connection to the ATmega32U4 and Arduino core files:
    * D17 | RxLED | SS
    * D14 | MISO
    Replace schematic package to match silkscreen from Brent's fix => [ https://github.com/sparkfun/SparkFun-Eagle-Libraries/issues/77#issuecomment-89820839 ]. Update the net for D17 to match silkscreen.
    This should not affect the overall functionality of the board. =P
2019-02-11 Update Arduino-Fio.brd
    Update labeling
2020-02-12 Update Old FioV3 Examples
    - adjust the output for the hardware UART in **Blinkies.ino** file to distinguish betweeh the serial monitor
    - add `Keyboard.begin()` in `setup()` for **SimpleKeyboard_HID.ino** (this appears to work without initializing it but it was added to be consistent with Arduino's reference example)
    - add `Mouse.begin()` in `setup()` to **SimpleJoystickMouse_HID.ino** (this appears to work without initializing it but it was added to be consistent with Arduino's reference example)
    - include the ability to invert the mouse using the joystick depending on the orientation of the joystick
    -autoformat
2025-06-27 Update README.md
    Updating link

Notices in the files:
parts and their libraries:
SparkFun-Capacitors: Licensing: CC v3.0 Share-Alike You are welcome to use this library for commercial purposes.
SparkFun-Aesthetics: Released under the Creative Commons Attribution Share-Alike 3.0 License
SparkFun-Aesthetics: http://creativecommons.org/licenses/by-sa/3.0
